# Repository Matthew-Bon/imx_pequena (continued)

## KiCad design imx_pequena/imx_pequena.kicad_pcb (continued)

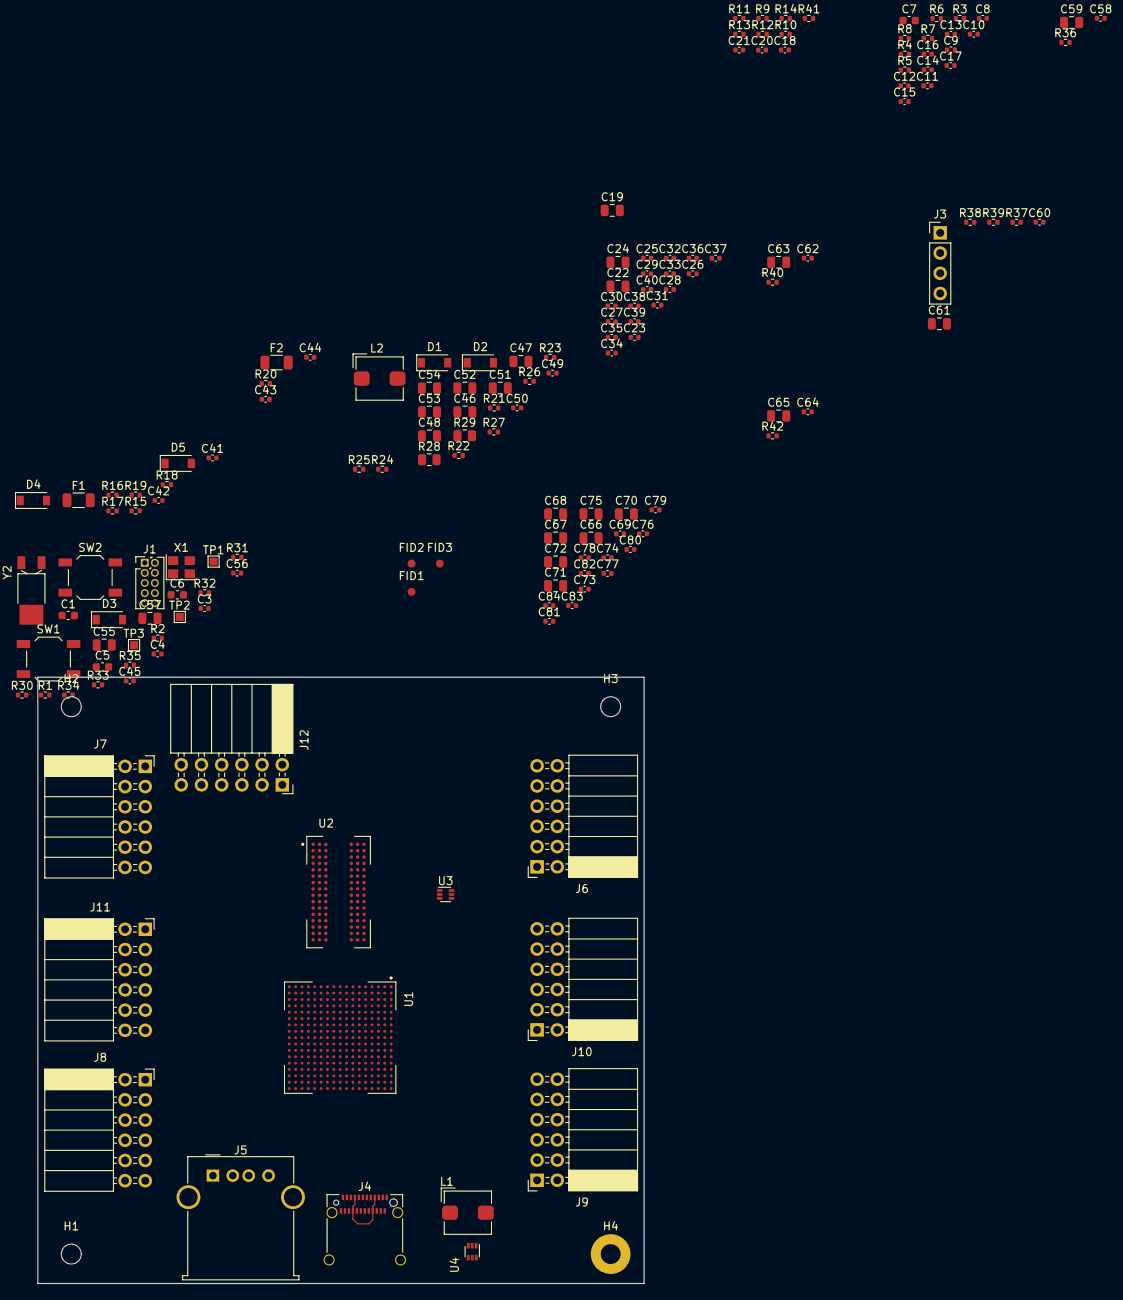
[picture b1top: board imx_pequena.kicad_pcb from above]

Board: 6 copper layers, 76.2 x 76.2 mm, 164 parts (1 on the bottom side), 165 nets.

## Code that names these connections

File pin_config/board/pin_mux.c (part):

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  - {pin_num: J14, peripheral: UART1, signal: uart_rts_b, pin_signal: UART1_RTS_B}
  - {pin_num: T16, peripheral: XTALOSC, signal: xtalosc_xtali, pin_signal: XTALI}
  - {pin_num: T17, peripheral: XTALOSC, signal: xtalosc_xtalo, pin_signal: XTALO}
  - {pin_num: B16, peripheral: ECSPI1, signal: ecspi_miso, pin_signal: GPIO3_IO28}
  - {pin_num: A14, peripheral: ECSPI1, signal: ecspi_mosi, pin_signal: GPIO3_IO27}
  - {pin_num: C12, peripheral: ECSPI1, signal: ecspi_rdy, pin_signal: GPIO3_IO17}
  - {pin_num: C14, peripheral: ECSPI1, signal: ecspi_sclk, pin_signal: GPIO3_IO25}
  - {pin_num: B14, peripheral: ECSPI1, signal: 'ecspi_ss, 0', pin_signal: GPIO3_IO26}
  - {pin_num: B10, peripheral: ECSPI1, signal: 'ecspi_ss, 1', pin_signal: GPIO3_IO10}
  - {pin_num: D11, peripheral: ECSPI1, signal: 'ecspi_ss, 3', pin_signal: GPIO3_IO12}
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  - {pin_num: B13, peripheral: GPIO3, signal: 'gpio_io, 22', pin_signal: GPIO3_IO22}
  - {pin_num: A13, peripheral: GPIO3, signal: 'gpio_io, 23', pin_signal: GPIO3_IO23}
  - {pin_num: D14, peripheral: GPIO3, signal: 'gpio_io, 24', pin_signal: GPIO3_IO24}
  - {pin_num: F17, peripheral: I2C2, signal: i2c_scl, pin_signal: I2C2_SCL}
  - {pin_num: P15, peripheral: SJC, signal: sjc_mod, pin_signal: JTAG_MOD}
  - {pin_num: M14, peripheral: SJC, signal: sjc_tck, pin_signal: JTAG_TCK}
  - {pin_num: N16, peripheral: SJC, signal: sjc_tdi, pin_signal: JTAG_TDI}
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  - {pin_num: H14, peripheral: UART2, signal: uart_rts_b, pin_signal: UART2_RTS_B}
  - {pin_num: J16, peripheral: UART2, signal: uart_rx, pin_signal: UART2_RX_DATA}
  - {pin_num: J17, peripheral: UART2, signal: uart_tx, pin_signal: UART2_TX_DATA}
  - {pin_num: G13, peripheral: I2C2, signal: i2c_sda, pin_signal: I2C2_SDA}
  - {pin_num: G16, peripheral: I2C1, signal: i2c_sda, pin_signal: UART4_RX_DATA}
  - {pin_num: L17, peripheral: GPIO1, signal: 'gpio_io, 3', pin_signal: GPIO1_IO03}
  - {pin_num: E15, peripheral: XTALOSC, signal: xtalosc_ref_clk_24m, pin_signal: KPP_COL1}
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
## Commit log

2023-06-09 Update gitignore
2023-06-09 Updated DRAM
    DRAM Schematic tentatively done
2023-06-10 SD card + pinot files
2023-06-11 Started IO section
    began adding crystals
2023-06-12 misc changes
    usb nets, crystal caps, etc...
2023-09-03 USB Updates
    Back in the saddle after moving. Added USB C and USB OTG symbols and supporting passives.
2023-11-19 Power Update
    Added 3v3 and 1.35V switchers
2023-12-02 Updated config
    Updated config file and some pins
2023-12-11 Power upates
    Added connections to power pins and decoupling caps
2024-01-13 Updated reset pins
    Updated reset pins
2024-01-15 Cleaned up NVCC pins
    Added 3v3 connections + decoupling caps to NVcc pins
2024-01-15 Updated pin mappings
2024-01-16 Updated pinouts
    Added misc uart changes
2024-01-28 Pinout updates
    Updated pinout files, changed pinout of gpio 1 and 3
2024-01-28 Added test points
    added test points
2024-02-08 Part Assignment
    Assigned GPIOs and assigned footprints to most parts
2024-02-18 lots of updates
    Set design rules, fixed ERC, etc....
2024-02-29 Layout updates
    moved pmod connectors
2024-03-02 fixed part alllocation
    fixed socket to pin header issue
